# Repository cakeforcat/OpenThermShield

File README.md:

# OpenThermShield
OpenTherm adapter/shield for the wemos d1 mini

The primary goal was low cost, speed and manufacturability. The components were gather in the [Edinburgh Hacklab](https://edinburghhacklab.com/) and milled on the PCB mill in 1 day

My boiler is a Vokera Unica 35C
## Photos

## Schematic
The pinout works if you flash the OTGateway firmware and swap the in/out pins in settings (like in the esphome.yaml), but imo esphome works better so if you're running HA highly recommend that approach

## PCB

## Case

Check out OpenThermShield - Case.3mf (support for bambu-studio). The case was also designed quickly so beware of the cover mount holes being too small. [The USB power supply used](https://www.amazon.co.uk/dp/B0DJVRCLWV)
# esphome.yaml
ESPHome config for the controller

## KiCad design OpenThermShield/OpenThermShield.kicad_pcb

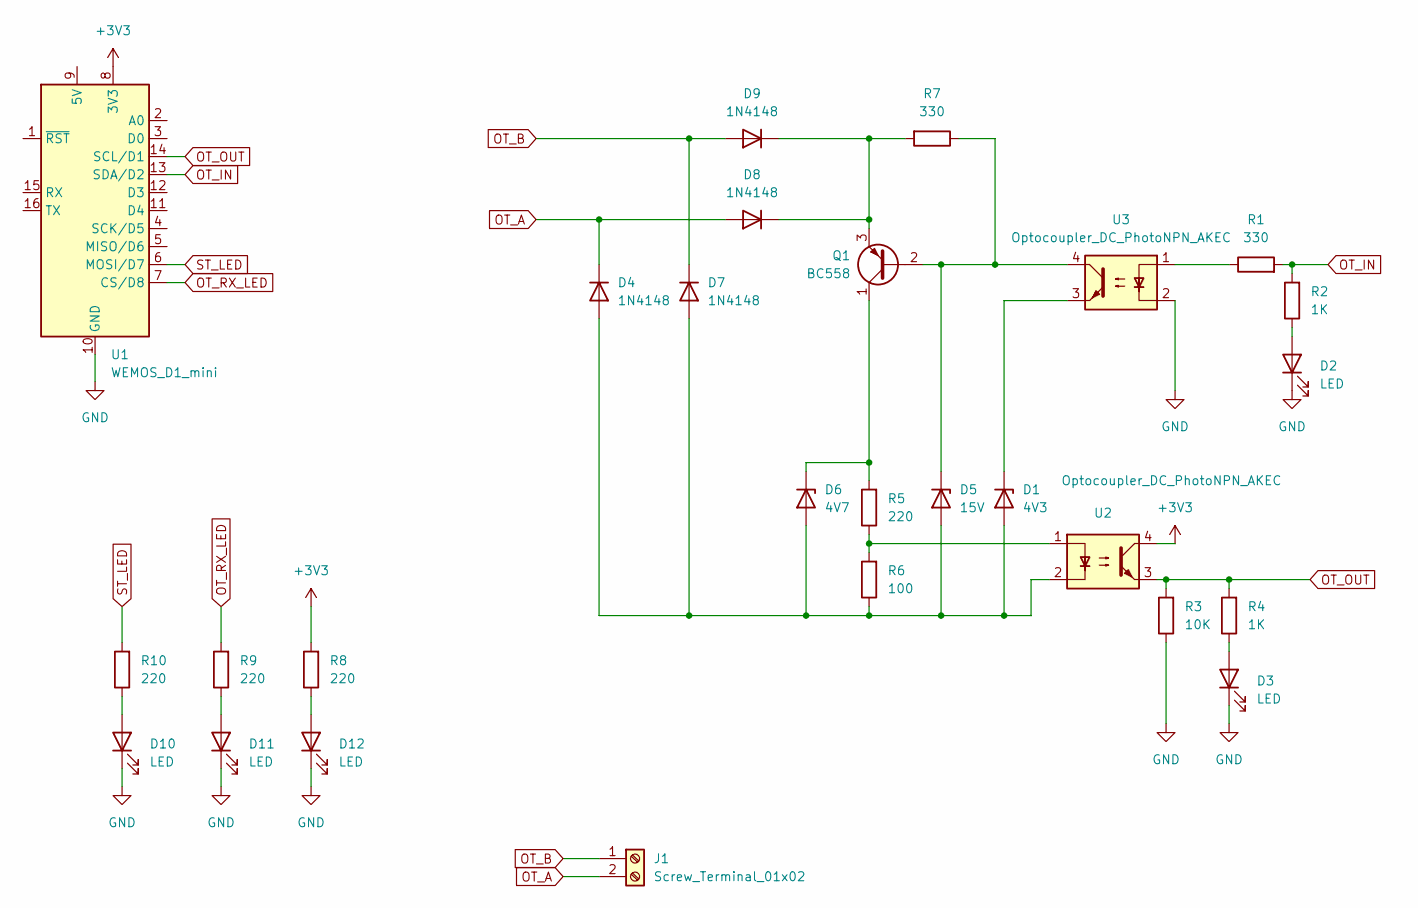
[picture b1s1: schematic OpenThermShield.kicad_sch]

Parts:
D1: 4V3; D_DO-41_SOD81_P10.16mm_Horizontal
D2, D3, D10, D11, D12: LED; LED_D3.0mm
D4, D7, D8, D9: 1N4148; D_DO-35_SOD27_P7.62mm_Horizontal
D5: 15V; D_DO-41_SOD81_P10.16mm_Horizontal
D6: 4V7; D_DO-41_SOD81_P10.16mm_Horizontal
J1: Screw_Terminal_01x02; TerminalBlock_MaiXu_MX126-5.0-02P_1x02_P5.00mm
Q1: BC558; TO-92_Inline
R1, R7: 330; R_Axial_DIN0204_L3.6mm_D1.6mm_P7.62mm_Horizontal
R2, R4: 1K; R_Axial_DIN0204_L3.6mm_D1.6mm_P7.62mm_Horizontal
R3: 10K; R_Axial_DIN0204_L3.6mm_D1.6mm_P7.62mm_Horizontal
R5, R8, R9, R10: 220; R_Axial_DIN0204_L3.6mm_D1.6mm_P7.62mm_Horizontal
R6: 100; R_Axial_DIN0204_L3.6mm_D1.6mm_P7.62mm_Horizontal
U1: WEMOS_D1_mini; WEMOS_D1_mini_light
U2, U3: Optocoupler_DC_PhotoNPN_AKEC; DIP-4_W7.62mm

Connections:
+3V3: R8.2, U1.8 (3V3), U2.4
GND: D2.1 (K), D3.1 (K), D10.1 (K), D11.1 (K), D12.1 (K), R3.1, U1.10 (GND), U3.2
unnamed: D1.2 (A), D4.2 (A), D5.2 (A), D6.2 (A), D7.2 (A), R6.1, U2.2
unnamed: D1.1 (K), U3.3
unnamed: D2.2 (A), R2.1
unnamed: D3.2 (A), R4.1
unnamed: D5.1 (K), Q1.2 (B), R7.1, U3.4
unnamed: D6.1 (K), Q1.1 (C), R5.2
unnamed: D8.1 (K), D9.1 (K), Q1.3 (E), R7.2
unnamed: D10.2 (A), R10.1
unnamed: D11.2 (A), R9.1
unnamed: D12.2 (A), R8.1
unnamed: R1.1, U3.1
unnamed: R5.1, R6.2, U2.1
OT_A: D4.1 (K), D8.2 (A), J1.2
OT_B: D7.1 (K), D9.2 (A), J1.1
OT_IN: R1.2, R2.2, U1.13 (SDA/D2)
OT_OUT: R3.2, R4.2, U1.14 (SCL/D1), U2.3
OT_RX_LED: R9.2, U1.7 (CS/D8)
ST_LED: R10.2, U1.6 (MOSI/D7)

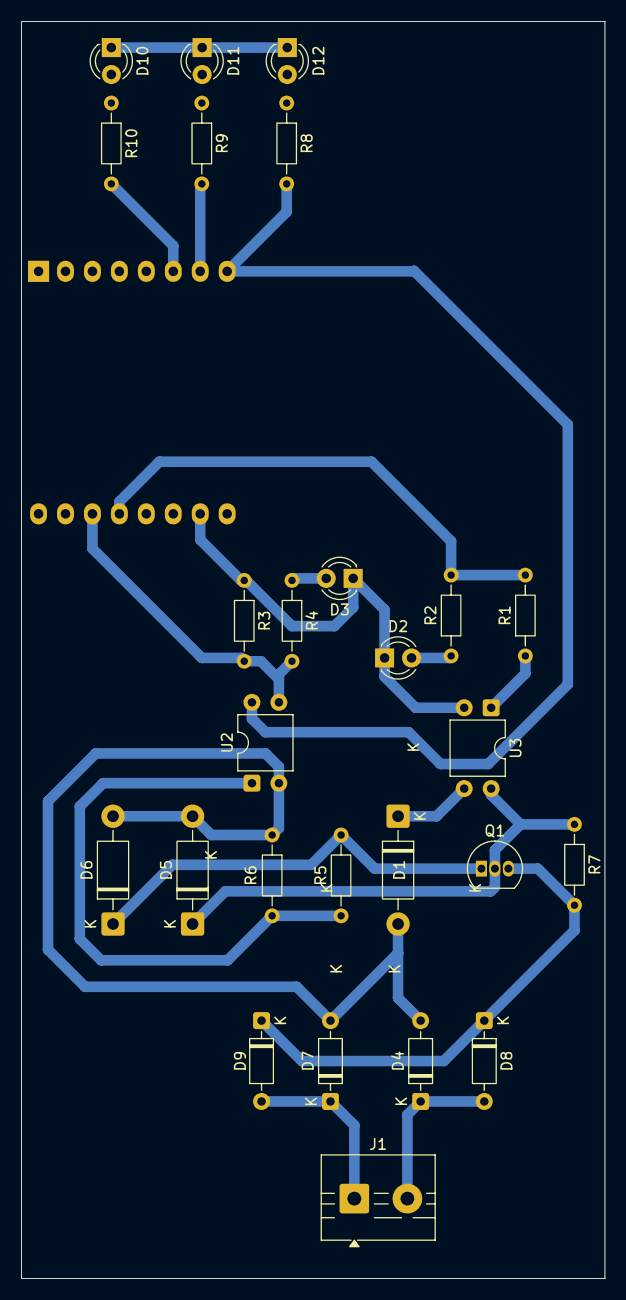
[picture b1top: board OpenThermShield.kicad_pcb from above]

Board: 2 copper layers, 55.0 x 118.5 mm, 27 parts (1 on the bottom side), 20 nets.

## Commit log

2025-11-24 i guess it's done lol
2025-12-02 docs
2026-01-03 update esphome
